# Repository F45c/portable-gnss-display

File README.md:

# Portable GNSS / GPS Display
### What it is
The Display shows a satellite map of your nearby surroundings with an indicator in the center of the device's location. It not only uses GPS satellites but also the european Galileo, BeiDou and some others.
With the UART connections and USB connectors, you can read the position with a phone or a computer.

### How it works
It uses the ublox neo m9n chip with an active antenna and an Esp32-C3 that extracts the position, calculates the tiles to draw on the screen and draws them together with a position mark on the display.
The tiles are stored on sd card slot in the tft display and are pre-downloaded on set sd card for a small area around my home town.

### Finished Module
I finished the PCB assembly. It was difficult to solder the tiny components and especially the SMD parts. Thankfully, with the help of solder flux and a heat gun, I was able to solder everything on the pcb.
The most annoying component was the USB-C connector because the pins are so tiny and would always bridge multiple together.

I downloaded a few tiles where I live and put them on an sd card. I had to censor the map mostly so I don't leak my address. The example image is below.

It's a very nice device but after all, I still use my phone more often than this.

(Redacted display because it shows my home location)

In the center, on the red + symbol is the gps position and on top is the N for north.

#### Technical Details
> The Neo M9N can be directly connected via USB-A Connector to an external device
>
>The Esp32 and Neo communicate over UART with baud rate 9600
>
>The Esp32 communicates with the display and sd card over SPI
>
>
>With some jumper pins, you can configure which part of the PCB is powered with what source.
>
>The UART pin headers are for using an external uart connection to read the position or communicate with the Esp32.
>This can also be configured using jumper pins

#### Components
> uBlox Neo M9N -> GNSS Receiver
>
> Esp32-C3 -> processor
>
>  1.8 inch TFT Display with SD CARD -> Display
>
> Active Antenna -> better reception
>
> MCP170XT-3302E -> 3.3V Linear Voltage Regulator

### Why I made this
I wanted to have a device showing my exact location reliably because google maps sometimes doesn't show my location when my phone has bad cellular reception (even with good gps reception).

I also like satellite maps instead of normal street lines maps to better see what's around me and since the satellite images aren't up to date, you can see how the world changed.

It's kind of an extra gadget that doesn't require a phone to work and, as mentioned, runs reliably all the time, can't be hacked etc.

### Schematic

#### Some mentionable parts
> 27 Ω resistors (22+5.1) between D+/D- lines to Neo for full-speed driver
>
> lots of capacitors around LDOs for stable voltage
>
> important bias T at antenna input for active antennas
>
> Neo VDD_USB needs to be pulled down when not in use
>
> Jumper pin configuring happening on the left
>
> Three power source inputs to choose from (USB-A, USB-C, battery)

### PCB Design
The first thing to mention is that the 1.8inch display has enough room and isn't blocked by any components. I made sure of that through the entire development process.

#### Key Aspects of the Design
> minimum track width = 0.3mm, most power traces = 0.5mm
> lots of vias around the Neo and antenna connector shielding from interference
> four mounting holes when I want to screw it onto something
> tried to make it as small as possible
> track from antenna to Neo Pin has 50ohm impedance
> Ground Plane

When routing on the back layer (ground plane), I tried to make short cuts between the tracks so that the ground plane works better and the path of the current is as short as possible.

Here is an example of this where you can see the spacing between the different tracks on the ground plane (blue layer)

### BOM

| Name | Purpose | Quantity | Total Cost (USD) | Link | Distributor |
|------|---------|----------|-------------------|------|--------------|
| PCB | PCB board | 1 | 5.50 | | JLCPCB |
| Display | 1.8 inch TFT display | 1 | 6.47 | [Link](https://www.amazon.com/Chiffonade-Display-Interface-128x160-Resolution/dp/B0FQJX2SJV/) | Amazon |
| Antenna | GPS Antenna | 1 | 7.99 | [Link](https://www.amazon.com/28dB-High-Active-Antenna-Built/dp/B0C3H6BKHC) | Amazon |
| PCBA | PCB Assembly Parts | 1 | 33.27 | | |

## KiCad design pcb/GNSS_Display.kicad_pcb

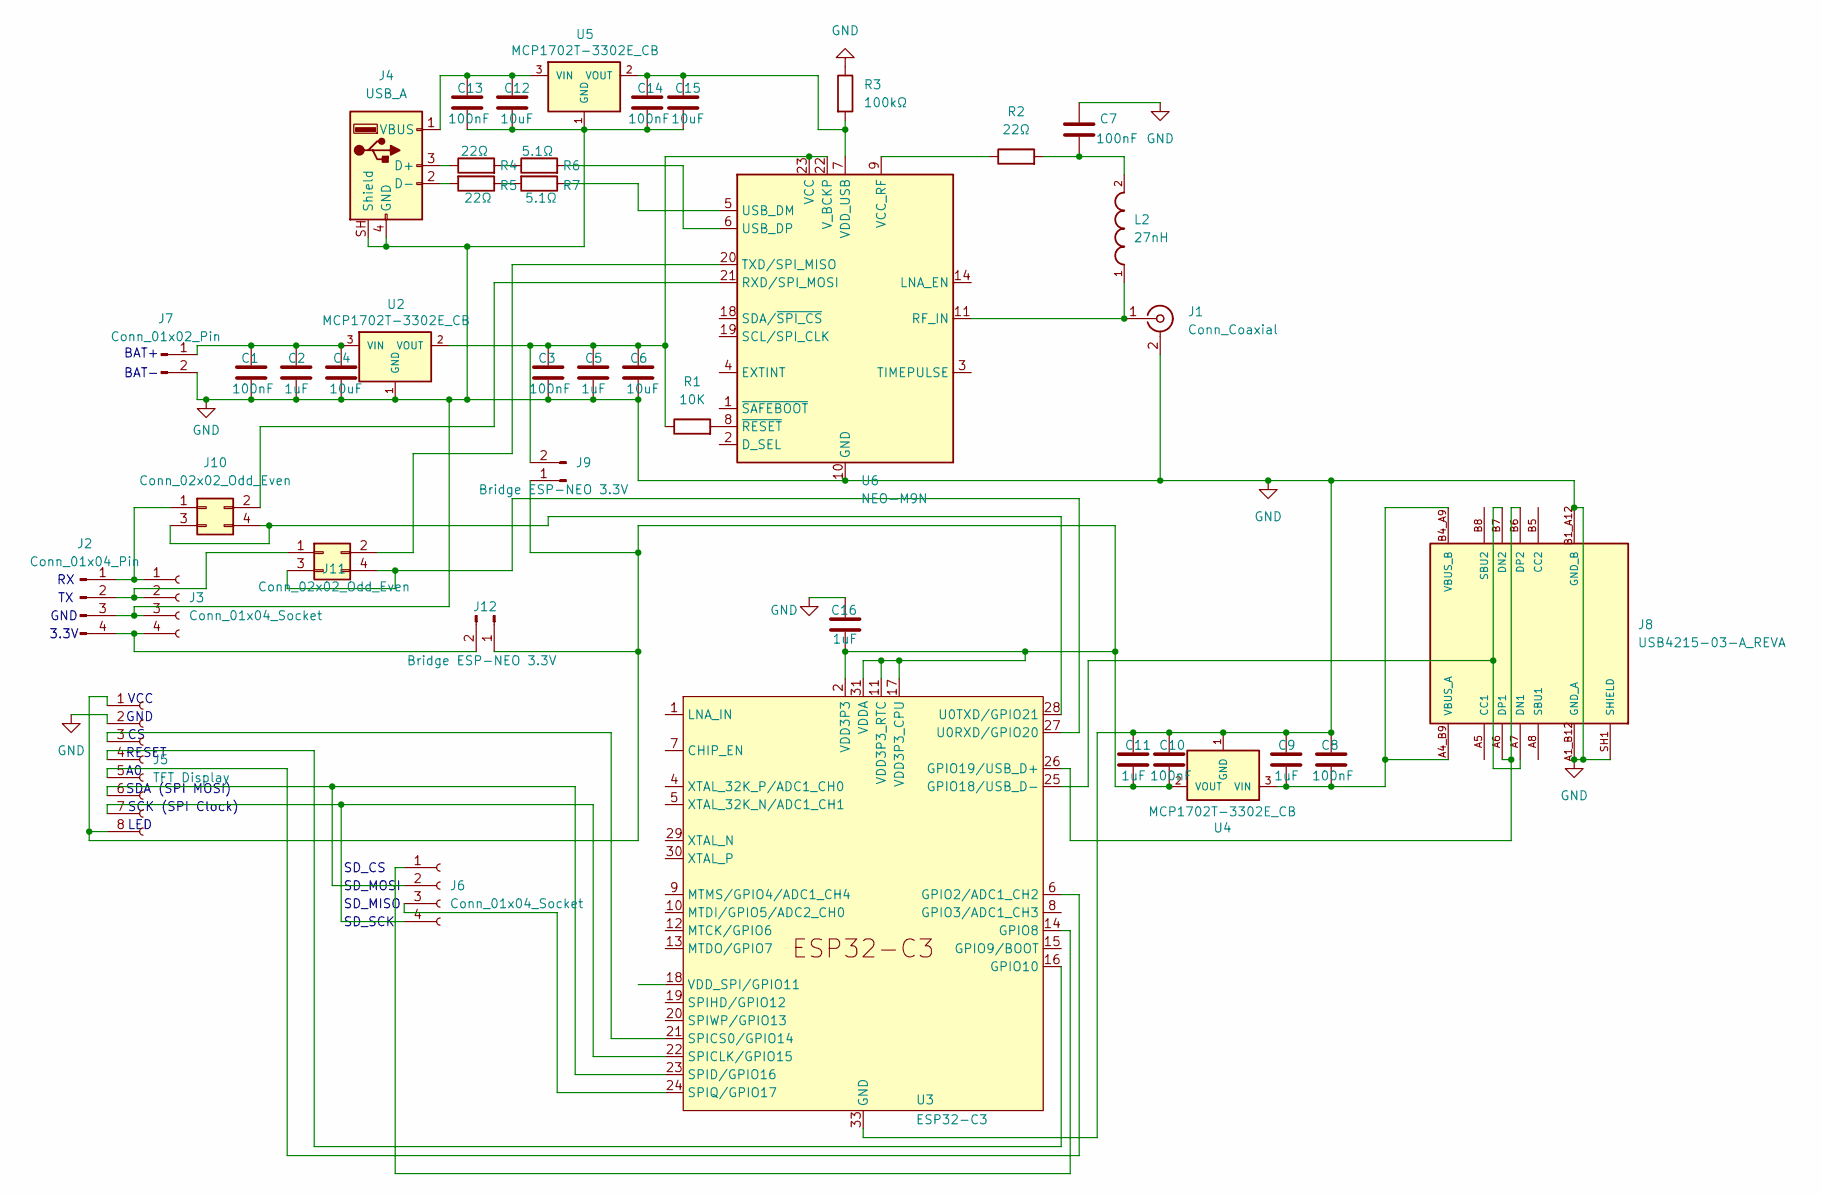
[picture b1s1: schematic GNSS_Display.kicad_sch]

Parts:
C1, C3, C7, C8, C10, C13, C14: 100nF; C_0603_1608Metric_Pad1.08x0.95mm_HandSolder
C2, C5, C9, C11, C16: 1uF; C_0603_1608Metric_Pad1.08x0.95mm_HandSolder
C4, C6, C12, C15: 10uF; C_0603_1608Metric_Pad1.08x0.95mm_HandSolder
J1: Conn_Coaxial; U.FL_Hirose_U.FL-R-SMT-1_Vertical
J2: Conn_01x04_Pin; PinHeader_1x04_P2.54mm_Vertical
J3, J6: Conn_01x04_Socket; PinSocket_1x04_P2.54mm_Vertical
J4: USB_A; USB_A_Molex_67643_Horizontal
J5: TFT Display; PinSocket_1x08_P2.54mm_Vertical
J7: Conn_01x02_Pin; PinHeader_1x02_P2.54mm_Vertical
J8: USB4215-03-A_REVA; GCT_USB4215-03-A_REVA; PARTREV A
J9, J12: Bridge ESP-NEO 3.3V; PinHeader_1x02_P2.54mm_Vertical
J10, J11: Conn_02x02_Odd_Even; PinHeader_2x02_P2.54mm_Vertical
L2: 27nH; INDC1005X55N
R1: 10K; R_0603_1608Metric_Pad0.98x0.95mm_HandSolder
R2, R4, R5: 22Ω; R_0603_1608Metric_Pad0.98x0.95mm_HandSolder
R3: 100kΩ; R_0603_1608Metric_Pad0.98x0.95mm_HandSolder
R6, R7: 5.1Ω; R_0603_1608Metric_Pad0.98x0.95mm_HandSolder
U2, U4, U5: MCP1702T-3302E_CB; SOT95P255X145-3N; MPN MCP1702T-3302E/CB
U3: ESP32-C3; QFN-32-1EP_5x5mm_P0.5mm_EP3.45x3.45mm
U6: NEO-M9N; ublox_NEO

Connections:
GND: C1.2, C2.2, C3.2, C4.2, C5.2, C6.2, C7.1, C8.1, C9.1, C10.1, C11.1, C12.2, C13.2, C14.2, C15.2, C16.2, J1.2 (Ext), J2.3, J3.3, J4.4 (GND), J4.SH (Shield), J5.2, J7.2, J8.A1_B12 (GND_A), J8.B1_A12 (GND_B), J8.SH1 (SHIELD), J8.SH2 (SHIELD), J8.SH3 (SHIELD), J8.SH4 (SHIELD), R3.1, U2.1 (GND), U3.33 (GND), U4.1 (GND), U5.1 (GND), U6.10 (GND), U6.12 (GND), U6.13 (GND), U6.24 (GND)
unnamed: C7.2, L2.2, R2.2
unnamed: J1.1 (In), L2.1, U6.11 (RF_IN)
unnamed: J4.3 (D+), R4.1
unnamed: J4.2 (D-), R5.2
unnamed: C12.1, C13.1, J4.1 (VBUS), U5.3 (VIN)
unnamed: J5.3, U3.21 (SPICS0/GPIO14)
unnamed: J5.4, U3.16 (GPIO10)
unnamed: J5.5, U3.6 (GPIO2/ADC1_CH2)
unnamed: J5.6, J6.2, U3.23 (SPID/GPIO16)
unnamed: J5.7, J6.4, U3.22 (SPICLK/GPIO15)
unnamed: J6.1, U3.14 (GPIO8)
unnamed: J6.3, U3.24 (SPIQ/GPIO17)
unnamed: C1.1, C2.1, C4.1, J7.1, U2.3 (VIN)
unnamed: J8.A7 (DN1), J8.B7 (DN2), U3.25 (GPIO18/USB_D-)
unnamed: J8.A6 (DP1), J8.B6 (DP2), U3.26 (GPIO19/USB_D+)
unnamed: C8.2, C9.2, J8.A4_B9 (VBUS_A), J8.B4_A9 (VBUS_B), U4.3 (VIN)
unnamed: C3.1, C5.1, C6.1, J9.2, R1.1, U2.2 (VOUT), U6.22 (V_BCKP), U6.23 (VCC)
unnamed: J2.1, J3.1, J10.1
unnamed: J10.2, U6.21 (RXD/SPI_MOSI)
unnamed: J10.3, J10.4, U3.28 (U0TXD/GPIO21)
unnamed: J2.2, J3.2, J11.1
unnamed: J11.2, U6.20 (TXD/SPI_MISO)
unnamed: J11.3, J11.4, U3.27 (U0RXD/GPIO20)
unnamed: C10.2, C11.2, C16.1, J5.1, J5.8, J9.1, J12.1, U3.2 (VDD3P3), U3.3 (VDD3P3), U3.11 (VDD3P3_RTC), U3.17 (VDD3P3_CPU), U3.31 (VDDA), U3.32 (VDDA), U4.2 (VOUT)
unnamed: J2.4, J3.4, J12.2
unnamed: R4.2, R6.1
unnamed: R5.1, R7.2
unnamed: C14.1, C15.1, R3.2, U5.2 (VOUT), U6.7 (VDD_USB)
unnamed: R7.1, U6.5 (USB_DM)
unnamed: R6.2, U6.6 (USB_DP)
unnamed: R2.1, U6.9 (VCC_RF)
unnamed: R1.2, U6.8 (~RESET)

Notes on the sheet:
SDA (SPI MOSI)
GND
SD_SCK
BAT+
SD_MISO
RESET
SD_MOSI
VCC
3.3V
SCK (SPI Clock)
BAT-
LED
SD_CS

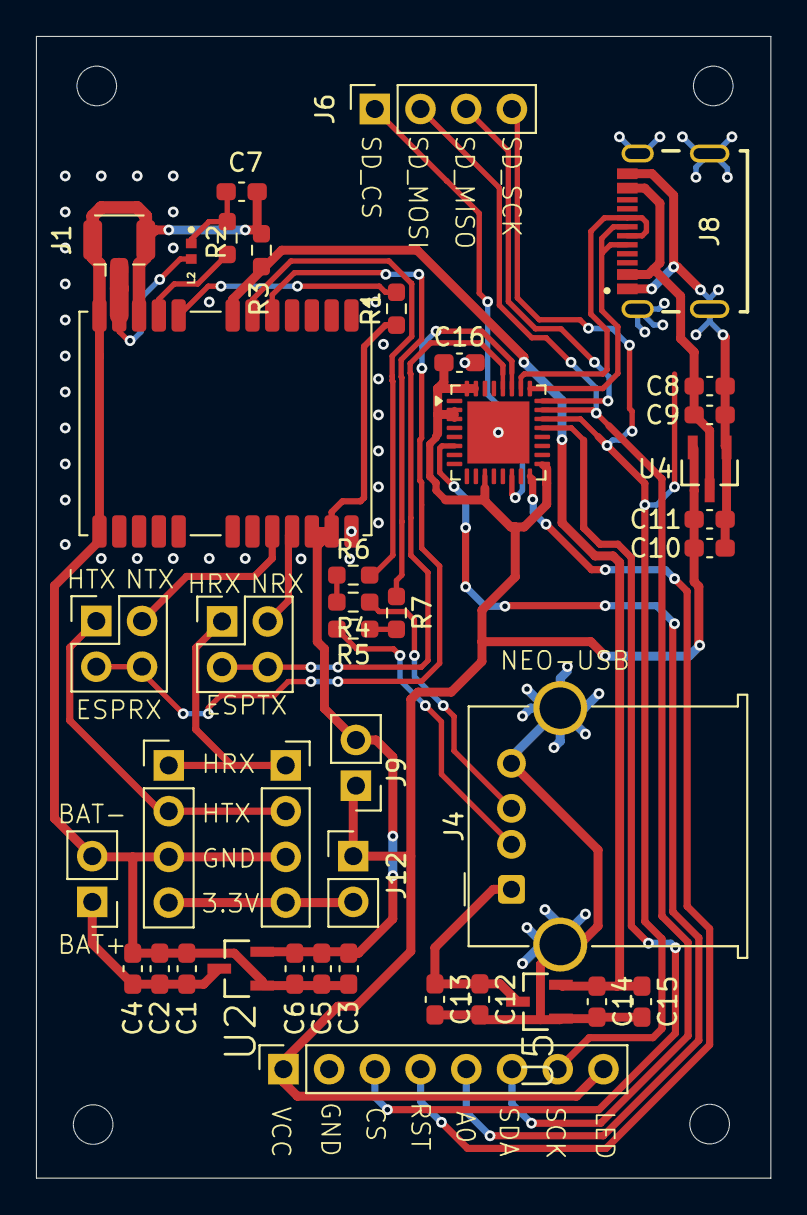
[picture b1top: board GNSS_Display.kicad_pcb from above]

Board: 2 copper layers, 40.8 x 63.4 mm, 41 parts (0 on the bottom side), 33 nets.

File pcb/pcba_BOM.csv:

"Reference","Qty","Value","DNP","Exclude from BOM","Exclude from Board","Footprint","Datasheet"
"C1,C3,C7,C8,C10,C13,C14","7","100nF","","","","Capacitor_SMD:C_0603_1608Metric_Pad1.08x0.95mm_HandSolder",""
"C2,C5,C9,C11,C16","5","1uF","","","","Capacitor_SMD:C_0603_1608Metric_Pad1.08x0.95mm_HandSolder",""
"C4,C6,C12,C15","4","10uF","","","","Capacitor_SMD:C_0603_1608Metric_Pad1.08x0.95mm_HandSolder",""
"J1","1","Conn_Coaxial","","","","Connector_Coaxial:U.FL_Hirose_U.FL-R-SMT-1_Vertical",""
"J2","1","Conn_01x04_Pin","","","","Connector_PinHeader_2.54mm:PinHeader_1x04_P2.54mm_Vertical",""
"J3,J6","2","Conn_01x04_Socket","","","","Connector_PinSocket_2.54mm:PinSocket_1x04_P2.54mm_Vertical",""
"J4","1","USB_A","","","","Connector_USB:USB_A_Molex_67643_Horizontal",""
"J5","1","TFT Display","","","","Connector_PinSocket_2.54mm:PinSocket_1x08_P2.54mm_Vertical",""
"J7","1","Conn_01x02_Pin","","","","Connector_PinHeader_2.54mm:PinHeader_1x02_P2.54mm_Vertical",""
"J8","1","USB4215-03-A_REVA","","","","USB4215-03-A_REVA:GCT_USB4215-03-A_REVA",""
"J9,J12","2","Bridge ESP-NEO 3.3V","","","","Connector_PinHeader_2.54mm:PinHeader_1x02_P2.54mm_Vertical",""
"J10,J11","2","Conn_02x02_Odd_Even","","","","Connector_PinHeader_2.54mm:PinHeader_2x02_P2.54mm_Vertical",""
"L2","1","27nH","","","","LQG15HS27NJ02D:INDC1005X55N",""
"R1","1","10K","","","","Resistor_SMD:R_0603_1608Metric_Pad0.98x0.95mm_HandSolder",""
"R2,R4,R5","3","22Ω","","","","Resistor_SMD:R_0603_1608Metric_Pad0.98x0.95mm_HandSolder",""
"R3","1","100kΩ","","","","Resistor_SMD:R_0603_1608Metric_Pad0.98x0.95mm_HandSolder",""
"R6,R7","2","5.1Ω","","","","Resistor_SMD:R_0603_1608Metric_Pad0.98x0.95mm_HandSolder",""
"U2,U4,U5","3","MCP1702T-3302E_CB","","","","MCP1702T-3302E_CB:SOT95P255X145-3N",""
"U3","1","ESP32-C3","","","","Package_DFN_QFN:QFN-32-1EP_5x5mm_P0.5mm_EP3.45x3.45mm","https://www.espressif.com/sites/default/files/documentation/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"
"U6","1","NEO-M9N","","","","RF_GPS:ublox_NEO","https://www.u-blox.com/sites/default/files/NEO-M9N-00B_DataS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"

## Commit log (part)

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2026-05-19 added KiCAD files and gerbers.zip
2026-05-19 added pcb image
2026-05-19 added display image
2026-05-19 added schematic image
2026-05-20 added example image of gnd plane routing
2026-05-20 rotated pcb image
2026-05-20 added pcb to readme
2026-05-27 added firmware for the esp32c3
2026-05-27 added 3d model
2026-05-27 added stl 3d model
2026-06-12 added bom.csv
2026-06-12 added bom to readme
